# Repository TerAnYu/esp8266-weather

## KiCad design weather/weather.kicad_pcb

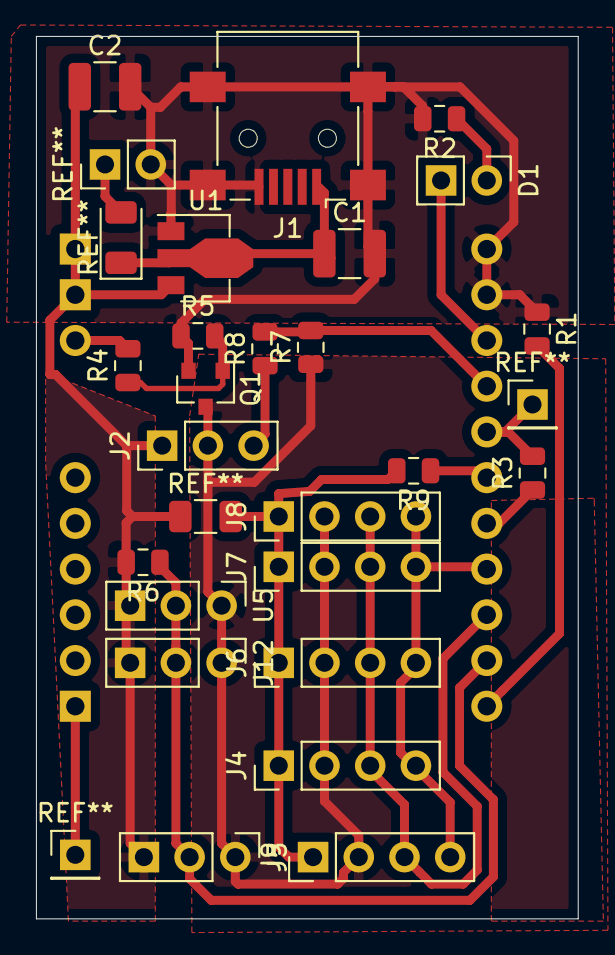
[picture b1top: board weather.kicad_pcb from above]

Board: 2 copper layers, 30.1 x 49.0 mm, 25 parts (1 on the bottom side), 17 nets.

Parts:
C1: 10u; C_1210_3225Metric
C2: 1u; C_1210_3225Metric
D1: LED; PinHeader_1x02_P2.54mm_Vertical
J1: USB_B_Mini; USB_Mini-B_Lumberg_2486_01_Horizontal
J2: Analog Sensor; PinHeader_1x03_P2.54mm_Vertical
J4, J9: BMP180; PinHeader_1x04_P2.54mm_Vertical
J5, J12: DALLAS; PinHeader_1x03_P2.54mm_Vertical
J6: HTU21; PinHeader_1x04_P2.54mm_Vertical
J7: SI7021; PinHeader_1x04_P2.54mm_Vertical
J8: OLED; PinHeader_1x04_P2.54mm_Vertical
Q1: 2N7002; SOT-23
R1, R7: 10K; R_0805_2012Metric
R2: 470R; R_0805_2012Metric
R3: 3K3; R_0805_2012Metric
R4: 100R; R_0805_2012Metric
R5: 100K; R_0805_2012Metric
R6: 4K7; R_0805_2012Metric
R8: 22K; R_0805_2012Metric
R9: 3k3; R_0805_2012Metric
U1: 7773-A; SOT-89-3
U2: ESP-201
U5: DS18B20; PinHeader_1x03_P2.54mm_Vertical

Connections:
/ANALOG: R7.2, R8.2, U2.15
/DALLAS: J5.2, J12.2, R6.1, U2.21, U5.2
/MOSFET: R4.2, U2.9
/RTS: R3.2, U2.16
/scl: J4.3, J6.3, J7.3, J8.3, J9.3, U2.20
/sda: J4.4, J6.4, J7.4, J8.4, J9.4, U2.19
GND: C1.2, C2.2, J1.5, J1.6, Q1.2, R1.1, R2.2, R5.1, U1.1, U2.12, U2.13
GNDS: J2.2, J4.2, J5.1, J6.2, J7.2, J8.2, J9.2, J12.1, Q1.3, R7.1, U5.1
unnamed: C1.1, J1.1, U1.2
unnamed: D1.1, R2.1
unnamed: D1.2, U2.14
unnamed: J2.3, R8.1
unnamed: Q1.1, R4.1, R5.2
unnamed: R1.2, U2.22
unnamed: R3.1, U2.18
unnamed: R9.1, U2.17
VCC: C2.1, J2.1, J4.1, J5.3, J6.1, J7.1, J8.1, J9.1, J12.3, R6.2, R9.2, U1.3, U2.10, U2.11, U5.3

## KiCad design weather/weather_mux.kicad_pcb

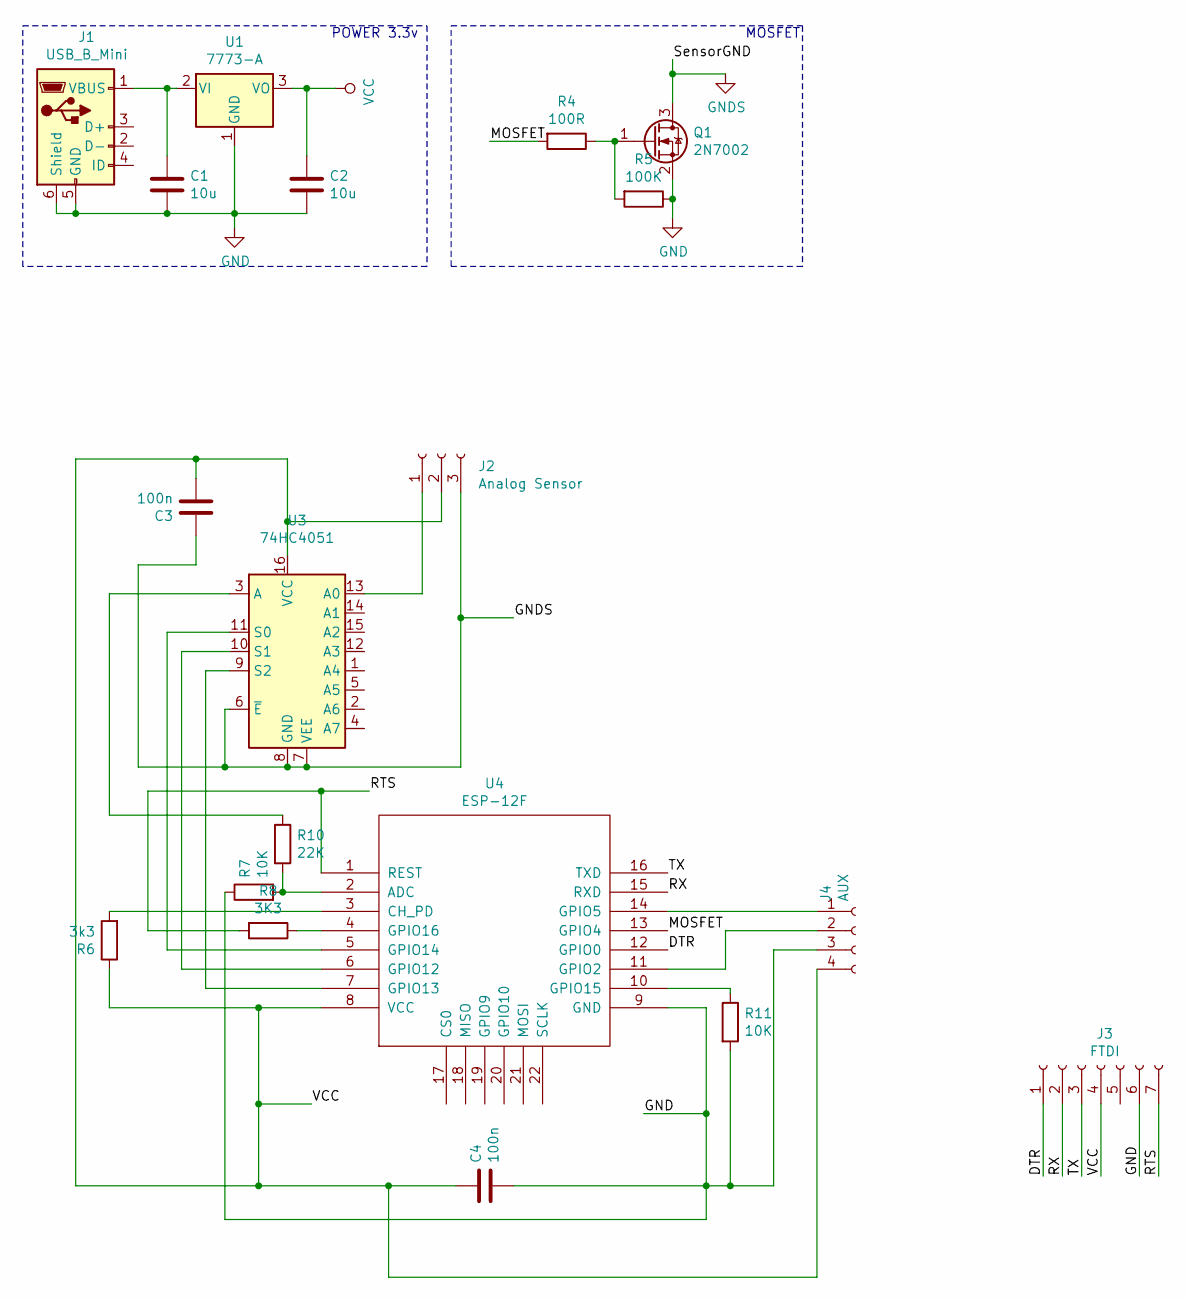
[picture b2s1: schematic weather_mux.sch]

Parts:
C1, C2: 10u; C_1210_3225Metric
C3, C4: 100n; C_1210_3225Metric
J1: USB_B_Mini; USB_Micro-B_Wuerth_629105150521
J2: Analog Sensor; PinHeader_1x03_P2.54mm_Vertical
J3: FTDI; PinHeader_1x07_P2.54mm_Vertical
J4: AUX; PinHeader_1x04_P2.54mm_Vertical
Q1: 2N7002; SOT-23
R4: 100R; R_0805_2012Metric
R5: 100K; R_0805_2012Metric
R6: 3k3; R_0805_2012Metric
R7, R11: 10K; R_0805_2012Metric
R8: 3K3; R_0805_2012Metric
R10: 22K; R_0805_2012Metric
U1: 7773-A; SOT-89-3
U3: 74HC4051; SOIC-16_3.9x9.9mm_P1.27mm
U4: ESP-12F; ESP-12E_SMD

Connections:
/DTR: J3.1, U4.12 (GPIO0)
/MOSFET: R4.2, U4.13 (GPIO4)
/RTS: J3.7, R8.2, U4.1 (REST)
/RX: J3.2, U4.15 (RXD)
/TX: J3.3, U4.16 (TXD)
GND: C1.2, C2.2, C4.2, J1.5 (GND), J1.6 (Shield), J3.6, J4.3, Q1.2 (S), R5.1, R7.1, R11.2, U1.1 (GND), U4.9 (GND)
GNDS: C3.1, J2.3, Q1.3 (D), U3.6 (~E), U3.7 (VEE), U3.8 (GND)
unnamed: C1.1, J1.1 (VBUS), U1.2 (VI)
unnamed: J2.1, U3.13 (A0)
unnamed: J4.1, U4.14 (GPIO5)
unnamed: J4.2, U4.11 (GPIO2)
unnamed: Q1.1 (G), R4.1, R5.2
unnamed: R6.2, U4.3 (CH_PD)
unnamed: R8.1, U4.4 (GPIO16)
unnamed: R10.1, U3.3 (A)
unnamed: R7.2, R10.2, U4.2 (ADC)
unnamed: R11.1, U4.10 (GPIO15)
unnamed: U3.9 (S2), U4.7 (GPIO13)
unnamed: U3.10 (S1), U4.6 (GPIO12)
unnamed: U3.11 (S0), U4.5 (GPIO14)
VCC: C2.1, C3.2, C4.1, J2.2, J3.4, J4.4, R6.1, U1.3 (VO), U3.16 (VCC), U4.8 (VCC)

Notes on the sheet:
MOSFET
POWER 3.3v

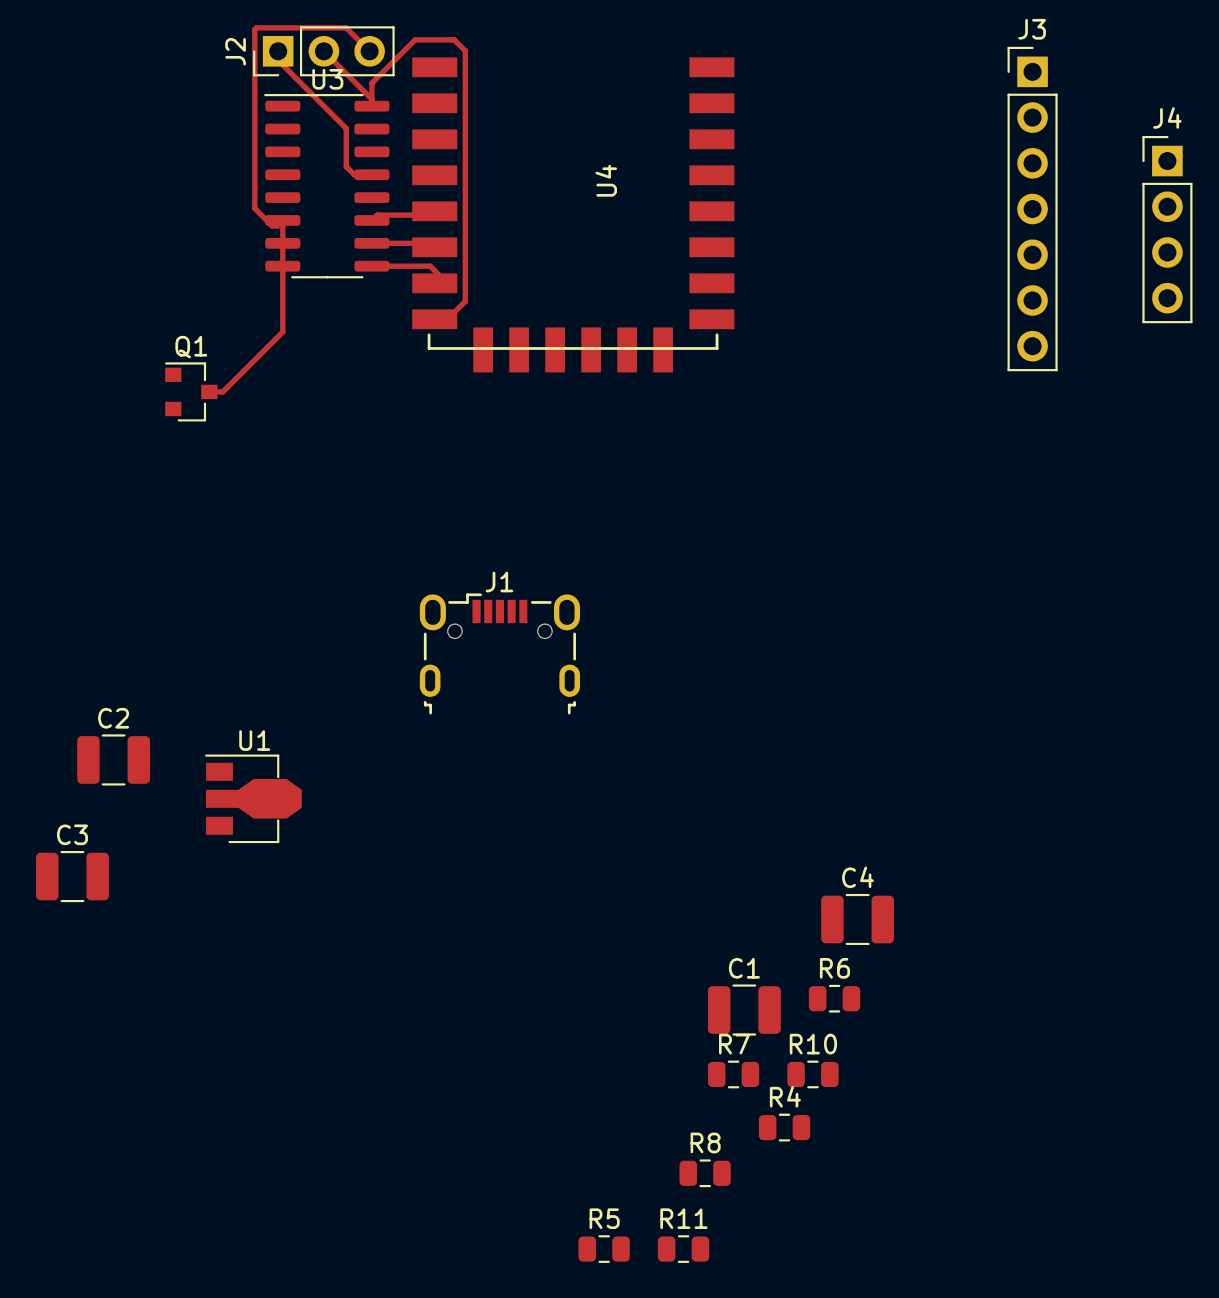
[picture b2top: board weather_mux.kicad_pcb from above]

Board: 2 copper layers, 19 parts (0 on the bottom side), 21 nets.

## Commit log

2020-02-26 kicad
    kicad files for esp8266-201
